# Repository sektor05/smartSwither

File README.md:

# Smart CAN Bus Switcher

This project is a DIY home automation solution for smart lighting, built around a custom PCB that fits into a standard electrical switch box. It uses a wired CAN bus for robust communication, controlled by a central single-board computer like Orange Pi. This approach provides industrial-grade reliability for your smart home.

## Key Features

*   **Dual Load Control:** Each module has two on-board triacs, allowing it to control two independent lighting groups.
*   **Dimming Functionality:** Supports dimmable LED lamps for smooth brightness adjustments, enabling "sunrise" or "soft evening light" scenes.
*   **Built-in Climate Monitoring:** An integrated temperature sensor in every switch turns your entire home into a climate monitoring network.
*   **Reliable Communication:** Operates over a 2-pair cable, with one pair for 12/24V power and the other for the CAN differential line.

## System Architecture

The heart of the system is a single-board computer (e.g., Orange Pi), which acts as the central brain.

1.  **Central Controller (Orange Pi):**
    *   Collects data from all switches via the CAN bus.
    *   Processes all automation logic (e.g., an "All Off" button at the entrance).
    *   Integrates with external services and voice assistants like Yandex Alice.
2.  **Smart Switch Modules:** Custom PCBs installed in wall switch boxes. They execute commands received from the controller and report status and sensor data.
3.  **CAN Bus:** The backbone of the system, providing a high-speed, reliable, and noise-immune communication link between the controller and all modules.

The server software can be implemented using platforms like **Home Assistant** or custom applications written in **Python/C++**, allowing for easy integration with smart home ecosystems. A command like *"Alice, set the living room light to 30%"* is sent to the Orange Pi, which instantly relays it to the appropriate module on the CAN bus to adjust the light level.

## Why CAN Bus over Zigbee/Wi-Fi?

For a new construction or major renovation, a wired solution offers significant advantages over popular wireless protocols.

| Characteristic      | This Solution (CAN Bus)                                   | Popular Wireless (Zigbee)                                |
| ------------------- | --------------------------------------------------------- | -------------------------------------------------------- |
| **Reliability**     | Maximum. Immune to interference from Wi-Fi or microwaves. | Depends on RF signal quality and the number of repeaters. |
| **Speed**           | Instantaneous response (milliseconds).                    | Delays are possible as nodes wake up or the mesh network adjusts. |
| **Power**           | Centralized. No batteries to replace in sensors.          | Requires battery changes or modules connected to a neutral wire. |
| **Scalability**     | Line length can extend to hundreds of meters.             | Limited by the radio signal range.                       |

The main benefit: a wired system is a "set it and forget it" solution. It won't fail because of a router firmware update or a new neighbor's Wi-Fi network.

## Project Structure

*   **/firmware/**: Contains firmware for the microcontroller (STM32/Arduino) on the switch modules. Includes projects for PlatformIO and STM32Cube.
*   **/hardware/**: Datasheets for components used in the project.
*   **/production/**: PCB manufacturing files, including KiCad project, Gerber files, and Bill of Materials (BOM).
*   **/software/**: Server-side applications and scripts for the Orange Pi.
*   **/documents/**: Design documents, manuals, and reports.

## Installation and Wiring

The system uses a 2-pair cable (e.g., KSPV or shielded twisted pair) for both power and data.

*   **Pair 1:** Power (GND / VCC)
*   **Pair 2:** Data (CAN-High / CAN-Low)

The PCB is designed to be compact, leaving enough space for wiring even in shallow switch boxes.

## Related Articles

*   [Умный свет своими руками: Делаем "умным" любой выключатель по шине CAN](https://project-wave.ru/2025/12/23/%d1%83%d0%bc%d0%bd%d1%8b%d0%b9-%d1%81%d0%b2%d0%b5%d0%b4-%d1%81%d0%b2%d0%be%d0%b8%d0%bc%d0%b8-%d1%80%d1%83%d0%ba%d0%b0%d0%bc%d0%b8-%d0%b4%d0%b5%d0%bb%d0%b0%d0%b5%d0%bc-%d0%82%d1%83%d0%bc%d0%bd%d1%8b%d0%bc/)

The next article will provide a detailed breakdown of the PCB schematic, component selection, and the board layout process in EasyEDA/KiCad.

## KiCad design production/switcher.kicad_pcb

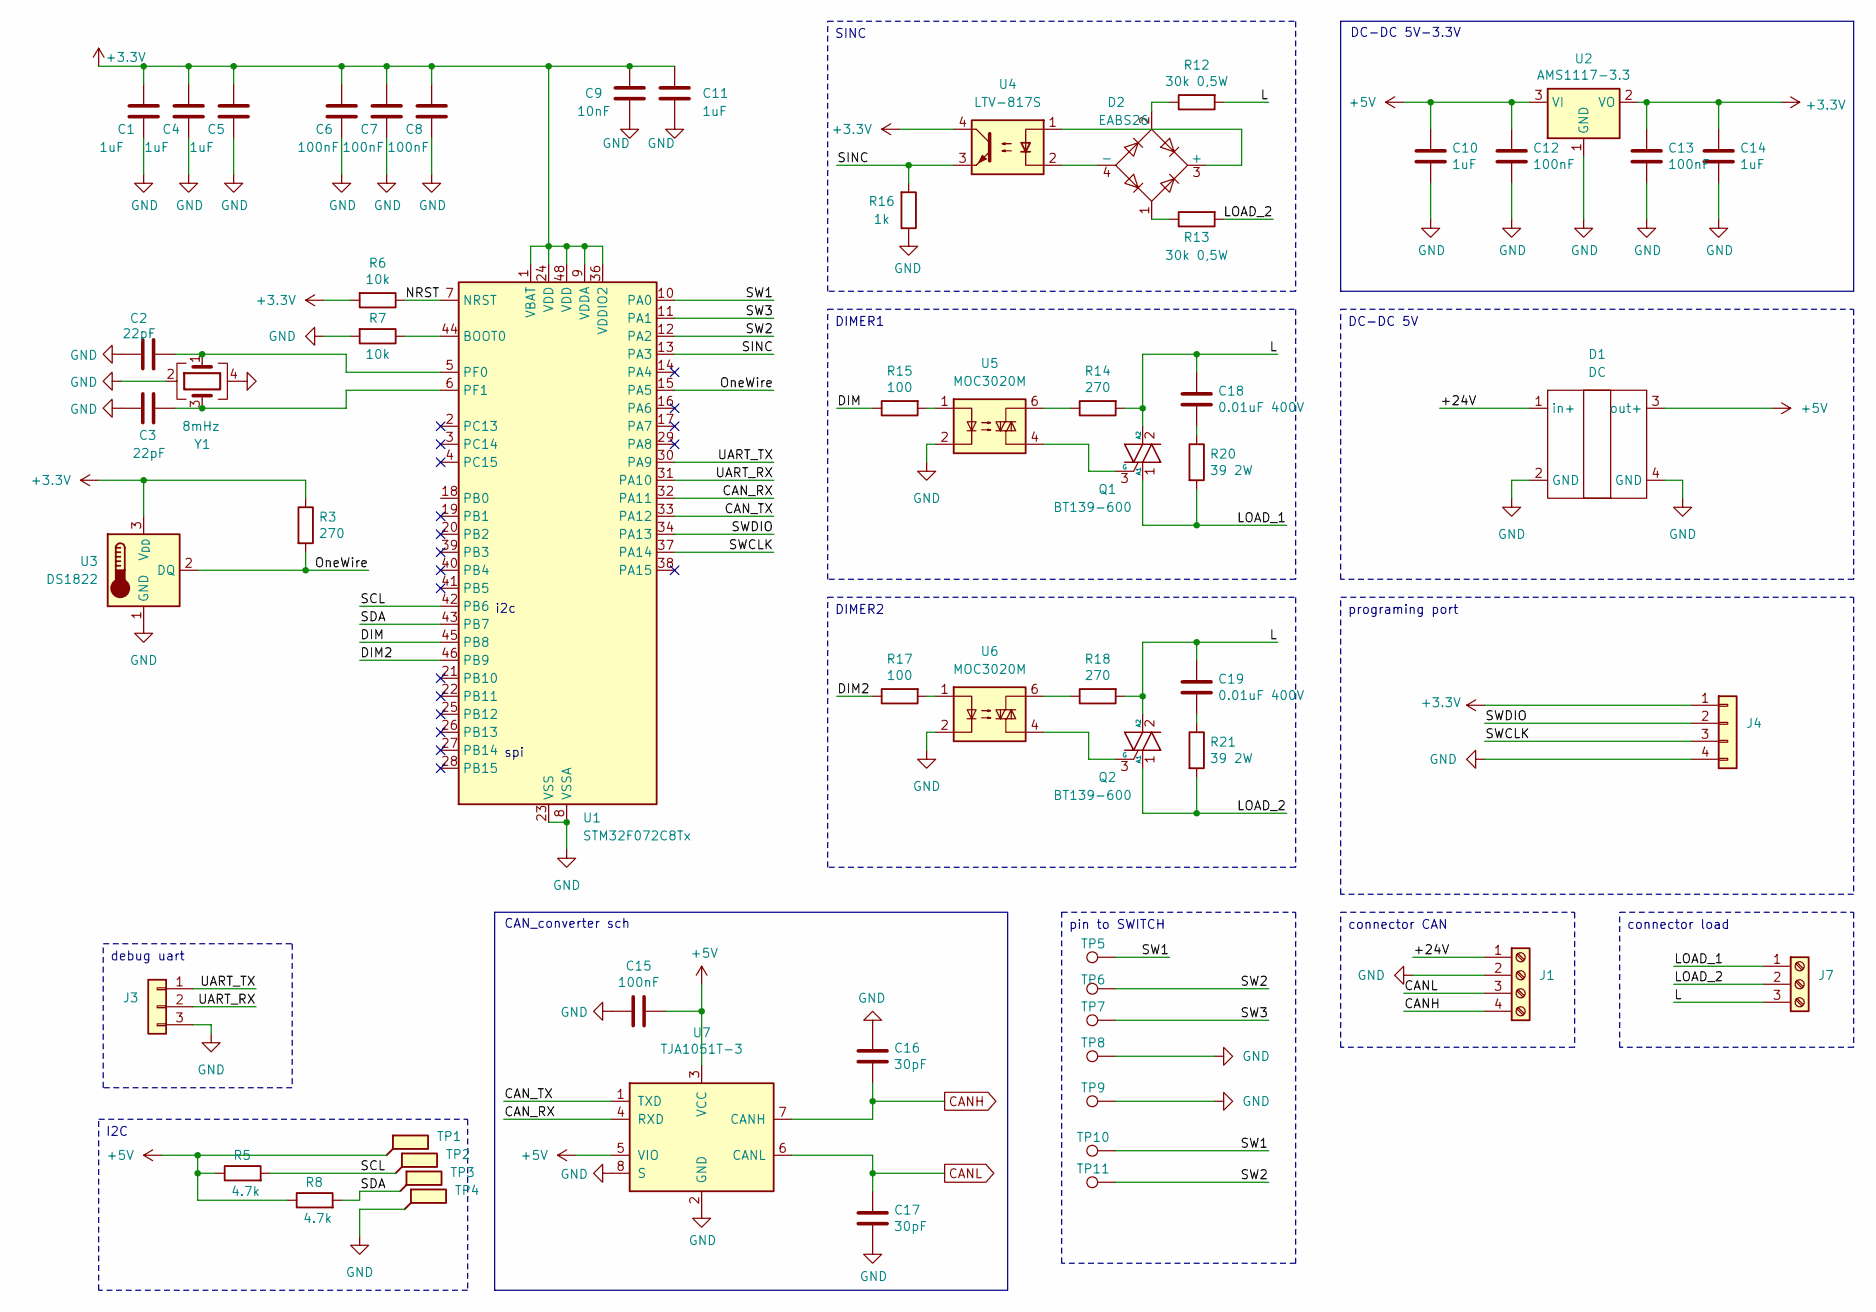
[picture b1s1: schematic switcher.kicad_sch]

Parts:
C1, C4, C5, C10, C11, C14: 1uF; C_0805_2012Metric
C2, C3: 22pF; C_0805_2012Metric
C6, C7, C8, C12, C13, C15: 100nF; C_0805_2012Metric
C9: 10nF; C_0805_2012Metric
C16, C17: 30pF; C_0805_2012Metric
C18, C19: 0.01uF 400V; C_Rect_L10.0mm_W2.5mm_P7.50mm_MKS4
D1: DC; 30V 3A
D2: EABS26; Diode_Bridge_Diotec_ABS
J1: Screw_Terminal_01x04; KF128-4P
J3: Conn_01x03
J4: Conn_01x04; PinHeader_1x04_P2.54mm_Vertical
J7: Screw_Terminal_01x03; KF128-3P
Q1, Q2: BT139-600; TO-220-3_Vertical
R3: 270; R_0805_2012Metric
R5, R8: 4.7k; R_0805_2012Metric
R6, R7: 10k; R_0805_2012Metric
R12, R13: 30k 0,5W; R_1206_3216Metric
R14, R18: 270; R_1206_3216Metric
R15, R17: 100; R_0805_2012Metric
R16: 1k; R_0805_2012Metric
R20, R21: 39 2W; R_Axial_DIN0414_L11.9mm_D4.5mm_P5.08mm_Vertical
TP1, TP2, TP3, TP4: TestPoint_Flag; TestPoint_Pad_1.0x1.0mm
TP5, TP6, TP7, TP8, TP9, TP10, TP11: TestPoint; TestPoint_Loop_D2.60mm_Drill1.6mm_Beaded
U1: STM32F072C8Tx; LQFP-48_7x7mm_P0.5mm
U2: AMS1117-3.3; SOT-223-3_TabPin2
U3: DS1822; TO-92_Inline
U4: LTV-817S; SMDIP-4_W9.53mm
U5, U6: MOC3020M; DIP-6_W7.62mm
U7: TJA1051T-3; SOIC-8_3.9x4.9mm_P1.27mm
Y1: 8mHz; Crystal_SMD_5032-4Pin_5.0x3.2mm

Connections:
+3.3V: C1.1, C4.1, C5.1, C6.1, C7.1, C8.1, C9.2, C11.1, C13.1, C14.1, J4.1, R3.1, R6.2, U1.1 (VBAT), U1.9 (VDDA), U1.24 (VDD), U1.36 (VDDIO2), U1.48 (VDD), U2.2 (VO), U3.3 (V_{DD}), U4.4
+5V: C10.1, C12.1, C15.1, D1.3 (out+), R5.1, R8.1, TP1.1, U2.3 (VI), U7.3 (VCC), U7.5 (VIO)
/+24V: D1.1 (in+), J1.1
/CAN_RX: U1.32 (PA11), U7.4 (RXD)
/CAN_TX: U1.33 (PA12), U7.1 (TXD)
/DIM: R15.1, U1.45 (PB8)
/DIM2: R17.1, U1.46 (PB9)
/L: C18.1, C19.1, J7.3, Q1.2 (A2), Q2.2 (A2), R12.2, R14.2, R18.2
/LOAD_1: J7.1, Q1.1 (A1), R20.2
/LOAD_2: J7.2, Q2.1 (A1), R13.2, R21.2
/NRST: R6.1, U1.7 (NRST)
/OneWire: R3.2, U1.15 (PA5), U3.2 (DQ)
/SCL: R5.2, TP2.1, U1.42 (PB6)
/SDA: R8.2, TP3.1, U1.43 (PB7)
/SINC: R16.2, U1.13 (PA3), U4.3
/SW1: TP5.1, TP10.1, U1.10 (PA0)
/SW2: TP6.1, TP11.1, U1.12 (PA2)
/SW3: TP7.1, U1.11 (PA1)
/SWCLK: J4.3, U1.37 (PA14)
/SWDIO: J4.2, U1.34 (PA13)
/UART_RX: J3.2, U1.31 (PA10)
/UART_TX: J3.1, U1.30 (PA9)
CANH: C16.2, J1.4, U7.7 (CANH)
CANL: C17.1, J1.3, U7.6 (CANL)
GND: C1.2, C2.1, C3.1, C4.2, C5.2, C6.2, C7.2, C8.2, C9.1, C10.2, C11.2, C12.2, C13.2, C14.2, C15.2, C16.1, C17.2, D1.2 (GND), D1.4 (GND), J1.2, J4.4, R7.2, R16.1, TP4.1, TP8.1, TP9.1, U1.8 (VSSA), U1.23 (VSS), U1.35 (VSS), U1.47 (VSS), U2.1 (GND), U3.1 (GND), U5.2, U6.2, U7.2 (GND), U7.8 (S), Y1.2, Y1.4
unnamed: C18.2, R20.1
unnamed: C19.2, R21.1
unnamed: D2.3 (+), U4.1
unnamed: D2.4 (-), U4.2
unnamed: D2.1, R13.1
unnamed: D2.2, R12.1
unnamed: Q1.3 (G), U5.4
unnamed: Q2.3 (G), U6.4
unnamed: R14.1, U5.6
unnamed: R15.2, U5.1
unnamed: R17.2, U6.1
unnamed: R18.1, U6.6
unnamed: R7.1, U1.44 (BOOT0)
unnamed: C2.2, U1.5 (PF0), Y1.1
unnamed: C3.2, U1.6 (PF1), Y1.3

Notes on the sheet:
spi
DC-DC 5V-3.3V
i2c
CAN_converter sch
DIMER1
programing port
DIMER2
pin to SWITCH
I2C
DC-DC 5V
SINC
connector CAN
connector load
debug uart

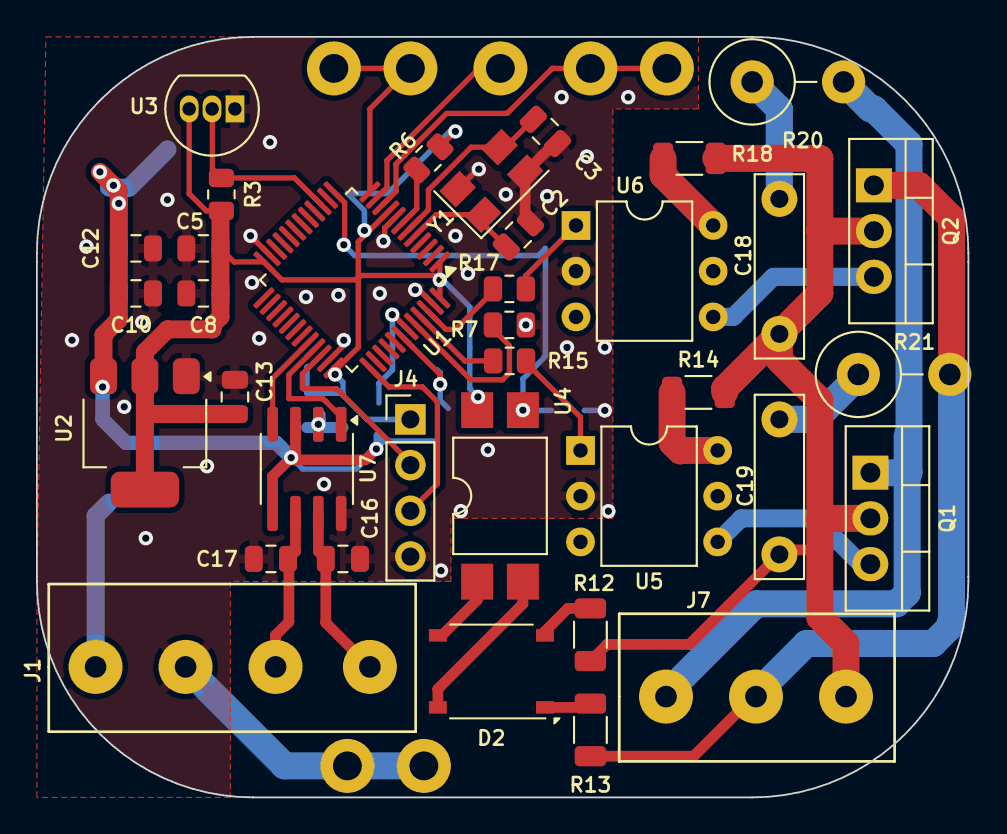
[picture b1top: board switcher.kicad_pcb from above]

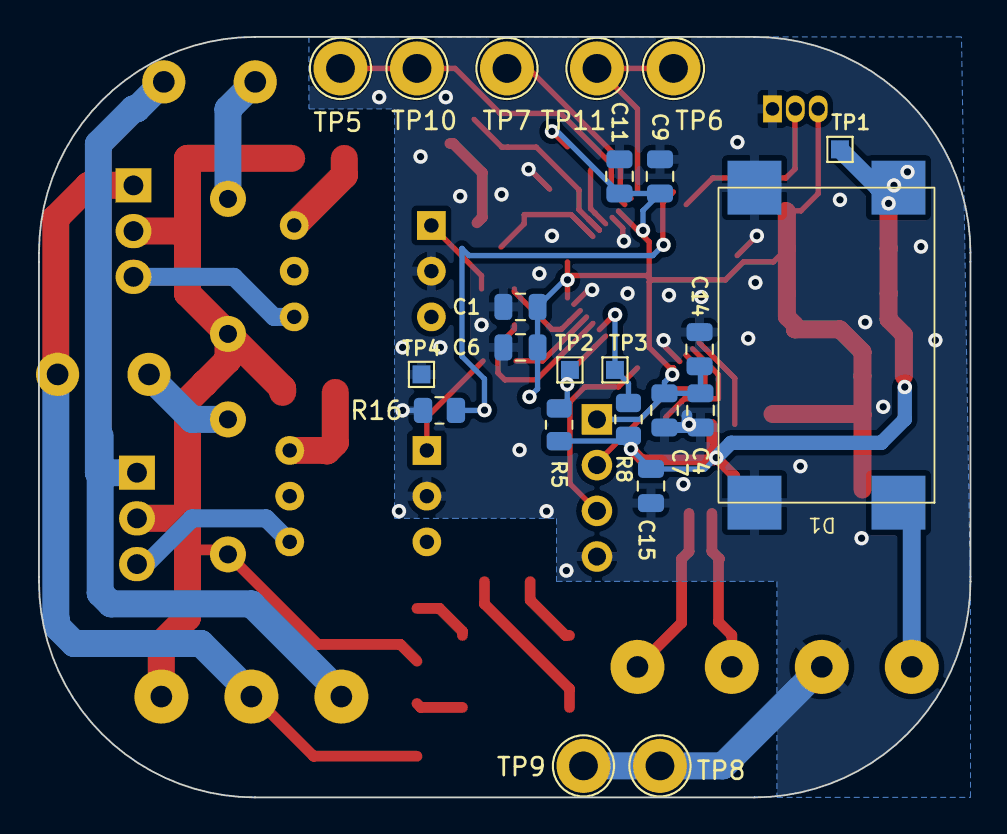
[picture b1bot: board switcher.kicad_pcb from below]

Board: 2 copper layers, 51.8 x 42.2 mm, 59 parts (23 on the bottom side), 38 nets.

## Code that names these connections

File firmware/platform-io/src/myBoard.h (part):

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//------------------определения пинов-------------------

// Пины управления диммерами
#define DIM_PIN PB8
#define DIM2_PIN PB9

// Входные пины
#define IN_1 PA0
#define IN_2 PA1
#define IN_3 PA2

// Пин детектора перехода через ноль (синхронизация)
#define SINC PA3

// CAN-шина пины
#define CAN_RX PA11
#define CAN_TX PA12

// I2C пины
#define I2C_SCL PB6
#define I2C_SDA PB7

// Пины для датчиков
#define ONE_W PA5
#define TEMP_SENSOR_PIN PA5  // Пин, к которому подключён LM335Z

// Адрес в EEPROM для хранения конфигурации
#define CONFIG_ADDR 10
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    analogReadResolution(12);  // Значения будут от 0 до 4095
 

    pinMode(DIM_PIN, OUTPUT);
    pinMode(DIM2_PIN, OUTPUT);

    digitalWrite(DIM_PIN, LOW);
    digitalWrite(DIM2_PIN, LOW);
   // HAL_GPIO_WritePin(GPIOB, GPIO_PIN_8, GPIO_PIN_SET);

    pinMode(ONE_W, OUTPUT);
    pinMode(SINC, INPUT);
    pinMode(IN_1, INPUT_PULLUP);
    pinMode(IN_2, INPUT_PULLUP);
    pinMode(IN_3, INPUT_PULLUP);
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
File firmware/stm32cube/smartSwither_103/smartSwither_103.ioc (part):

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Mcu.Name=STM32F103C(8-B)Tx
Mcu.Package=LQFP48
Mcu.UserName=STM32F103C8Tx
PA0-WKUP.GPIOParameters=GPIO_PuPd,GPIO_Label,GPIO_ModeDefaultEXTI
PA0-WKUP.GPIO_Label=SW1
PA0-WKUP.GPIO_ModeDefaultEXTI=GPIO_MODE_IT_RISING_FALLING
PA0-WKUP.GPIO_PuPd=GPIO_PULLUP
PA0-WKUP.Signal=GPXTI0
PA1.GPIOParameters=GPIO_PuPd,GPIO_Label,GPIO_ModeDefaultEXTI
PA1.GPIO_Label=SW3
PA1.GPIO_ModeDefaultEXTI=GPIO_MODE_IT_RISING_FALLING
PA1.GPIO_PuPd=GPIO_PULLUP
PA1.Signal=GPXTI1
PA11.Mode=CAN_Activate
PA11.Signal=CAN_RX
PA12.Mode=CAN_Activate
PA12.Signal=CAN_TX
PA13.Mode=Serial_Wire
PA13.Signal=SYS_JTMS-SWDIO
PA14.Mode=Serial_Wire
PA14.Signal=SYS_JTCK-SWCLK
PA2.GPIOParameters=GPIO_PuPd,GPIO_Label,GPIO_ModeDefaultEXTI
PA2.GPIO_Label=SW2
PA2.GPIO_ModeDefaultEXTI=GPIO_MODE_IT_RISING_FALLING
PA2.GPIO_PuPd=GPIO_PULLUP
PA2.Signal=GPXTI2
PA3.GPIOParameters=GPIO_Label,GPIO_ModeDefaultEXTI
PA3.GPIO_Label=SINC
PA3.GPIO_ModeDefaultEXTI=GPIO_MODE_IT_RISING
PA3.Signal=GPXTI3
PA5.Signal=ADCx_IN5
PB8.GPIOParameters=GPIO_Speed,GPIO_Label
PB8.GPIO_Label=DIM1
PB8.GPIO_Speed=GPIO_SPEED_FREQ_HIGH
PB8.Signal=GPIO_Output
PB9.GPIOParameters=GPIO_Speed,GPIO_Label
PB9.GPIO_Label=DIM2
PB9.GPIO_Speed=GPIO_SPEED_FREQ_HIGH
PB9.Signal=GPIO_Output
PD0-OSC_IN.Mode=HSE-External-Oscillator
PD0-OSC_IN.Signal=RCC_OSC_IN
PD1-OSC_OUT.Mode=HSE-External-Oscillator
PD1-OSC_OUT.Signal=RCC_OSC_OUT
RCC.SYSCLKFreq_VALUE=40000000
RCC.SYSCLKSource=RCC_SYSCLKSOURCE_PLLCLK
board=custom

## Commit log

2025-12-23 feat: Add .gitignore
2025-12-23 feat: Initial import of project files
2025-12-23 docs: Add link to related article in README
